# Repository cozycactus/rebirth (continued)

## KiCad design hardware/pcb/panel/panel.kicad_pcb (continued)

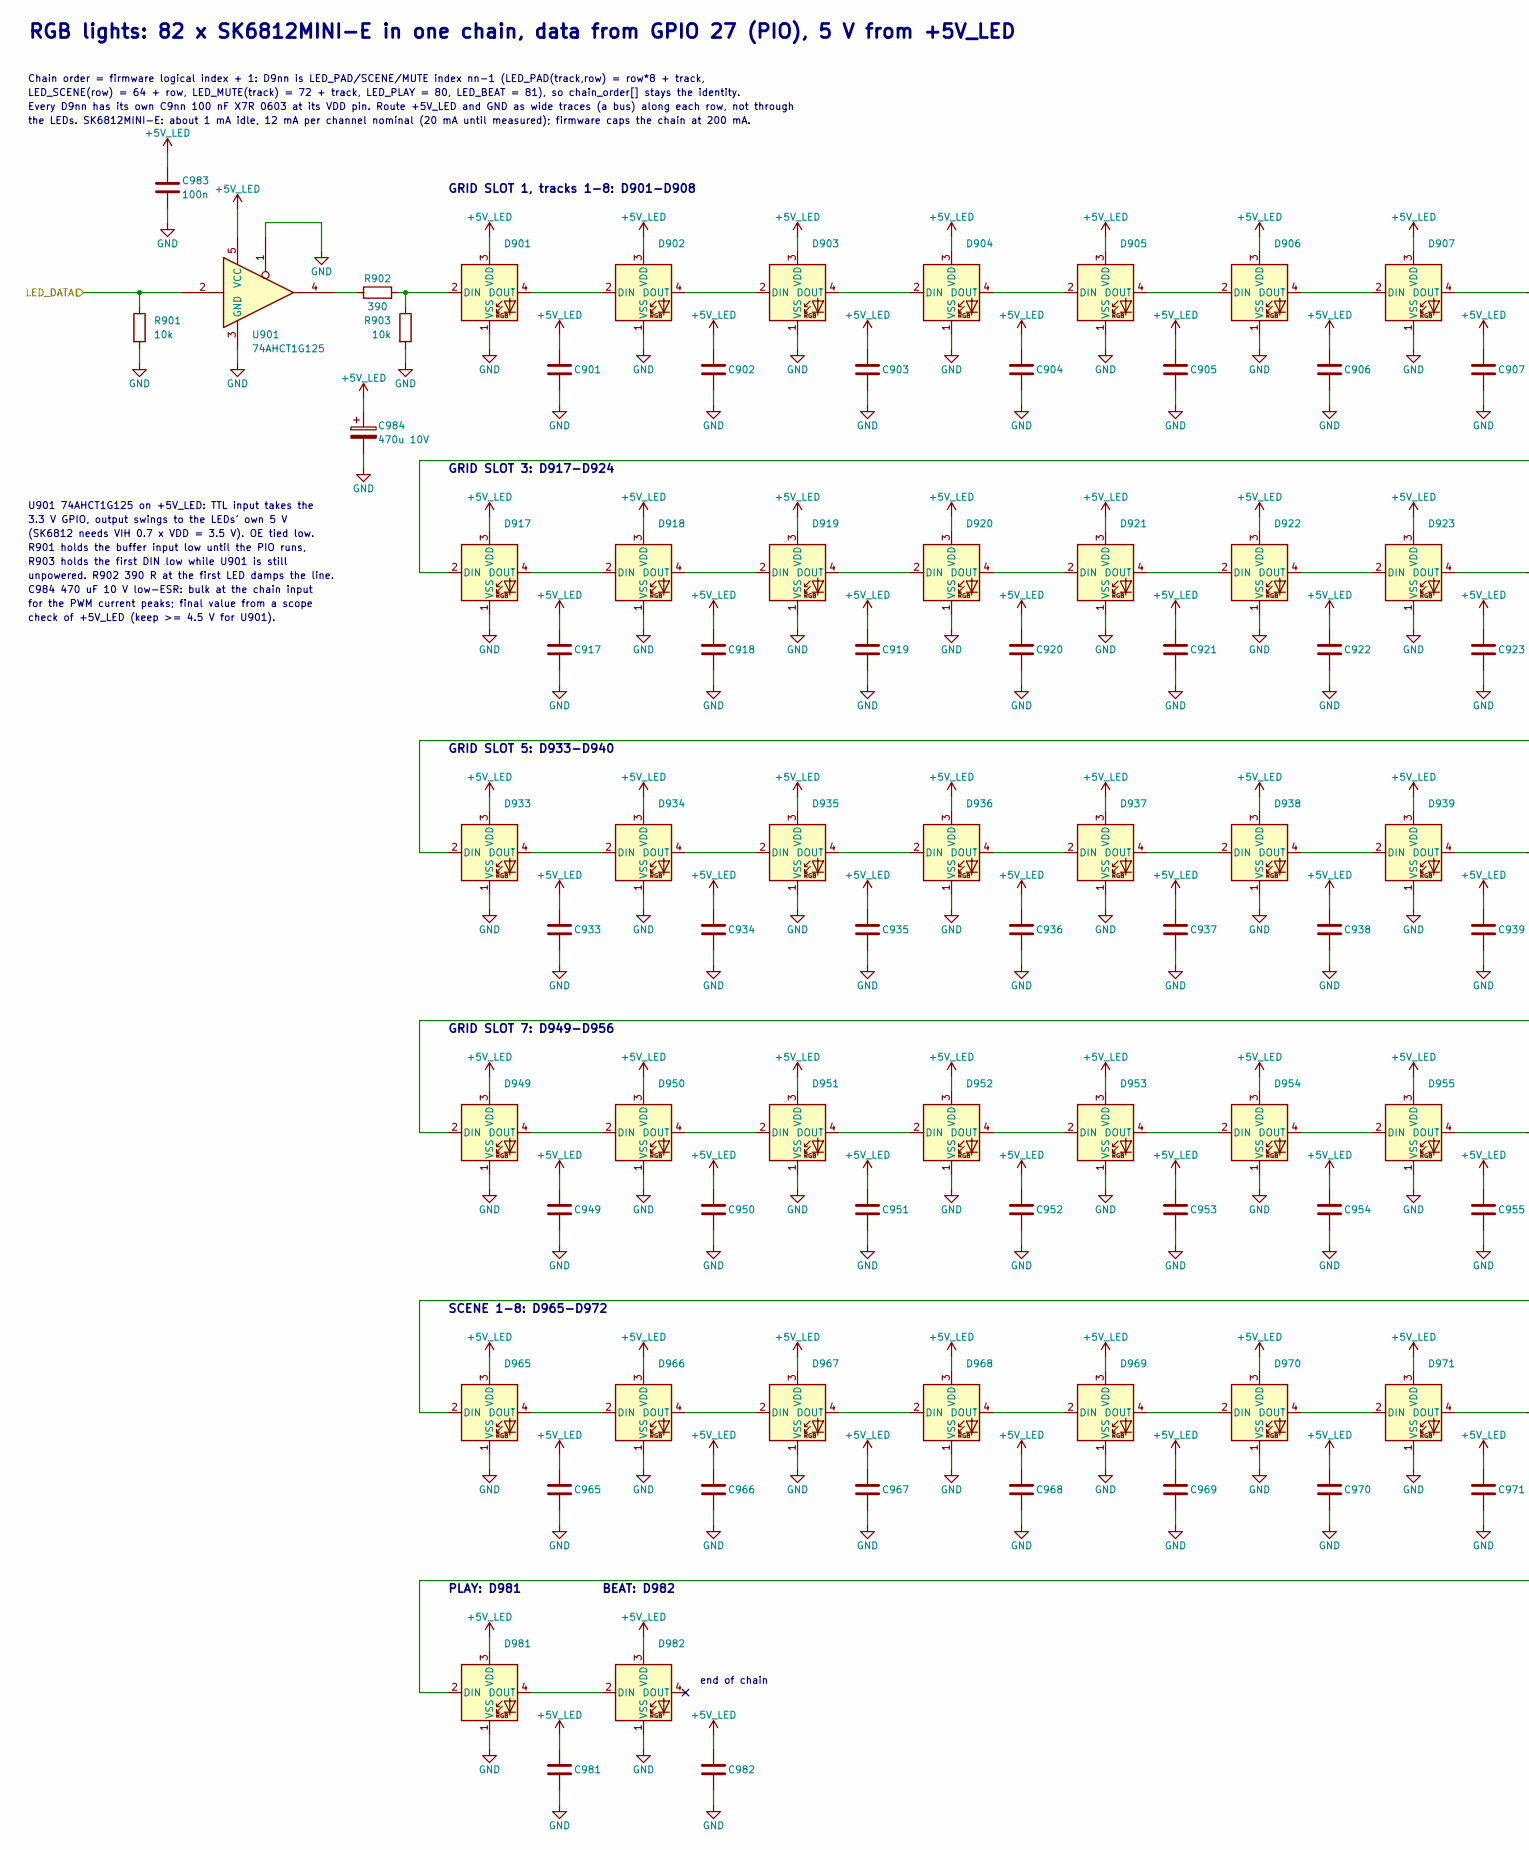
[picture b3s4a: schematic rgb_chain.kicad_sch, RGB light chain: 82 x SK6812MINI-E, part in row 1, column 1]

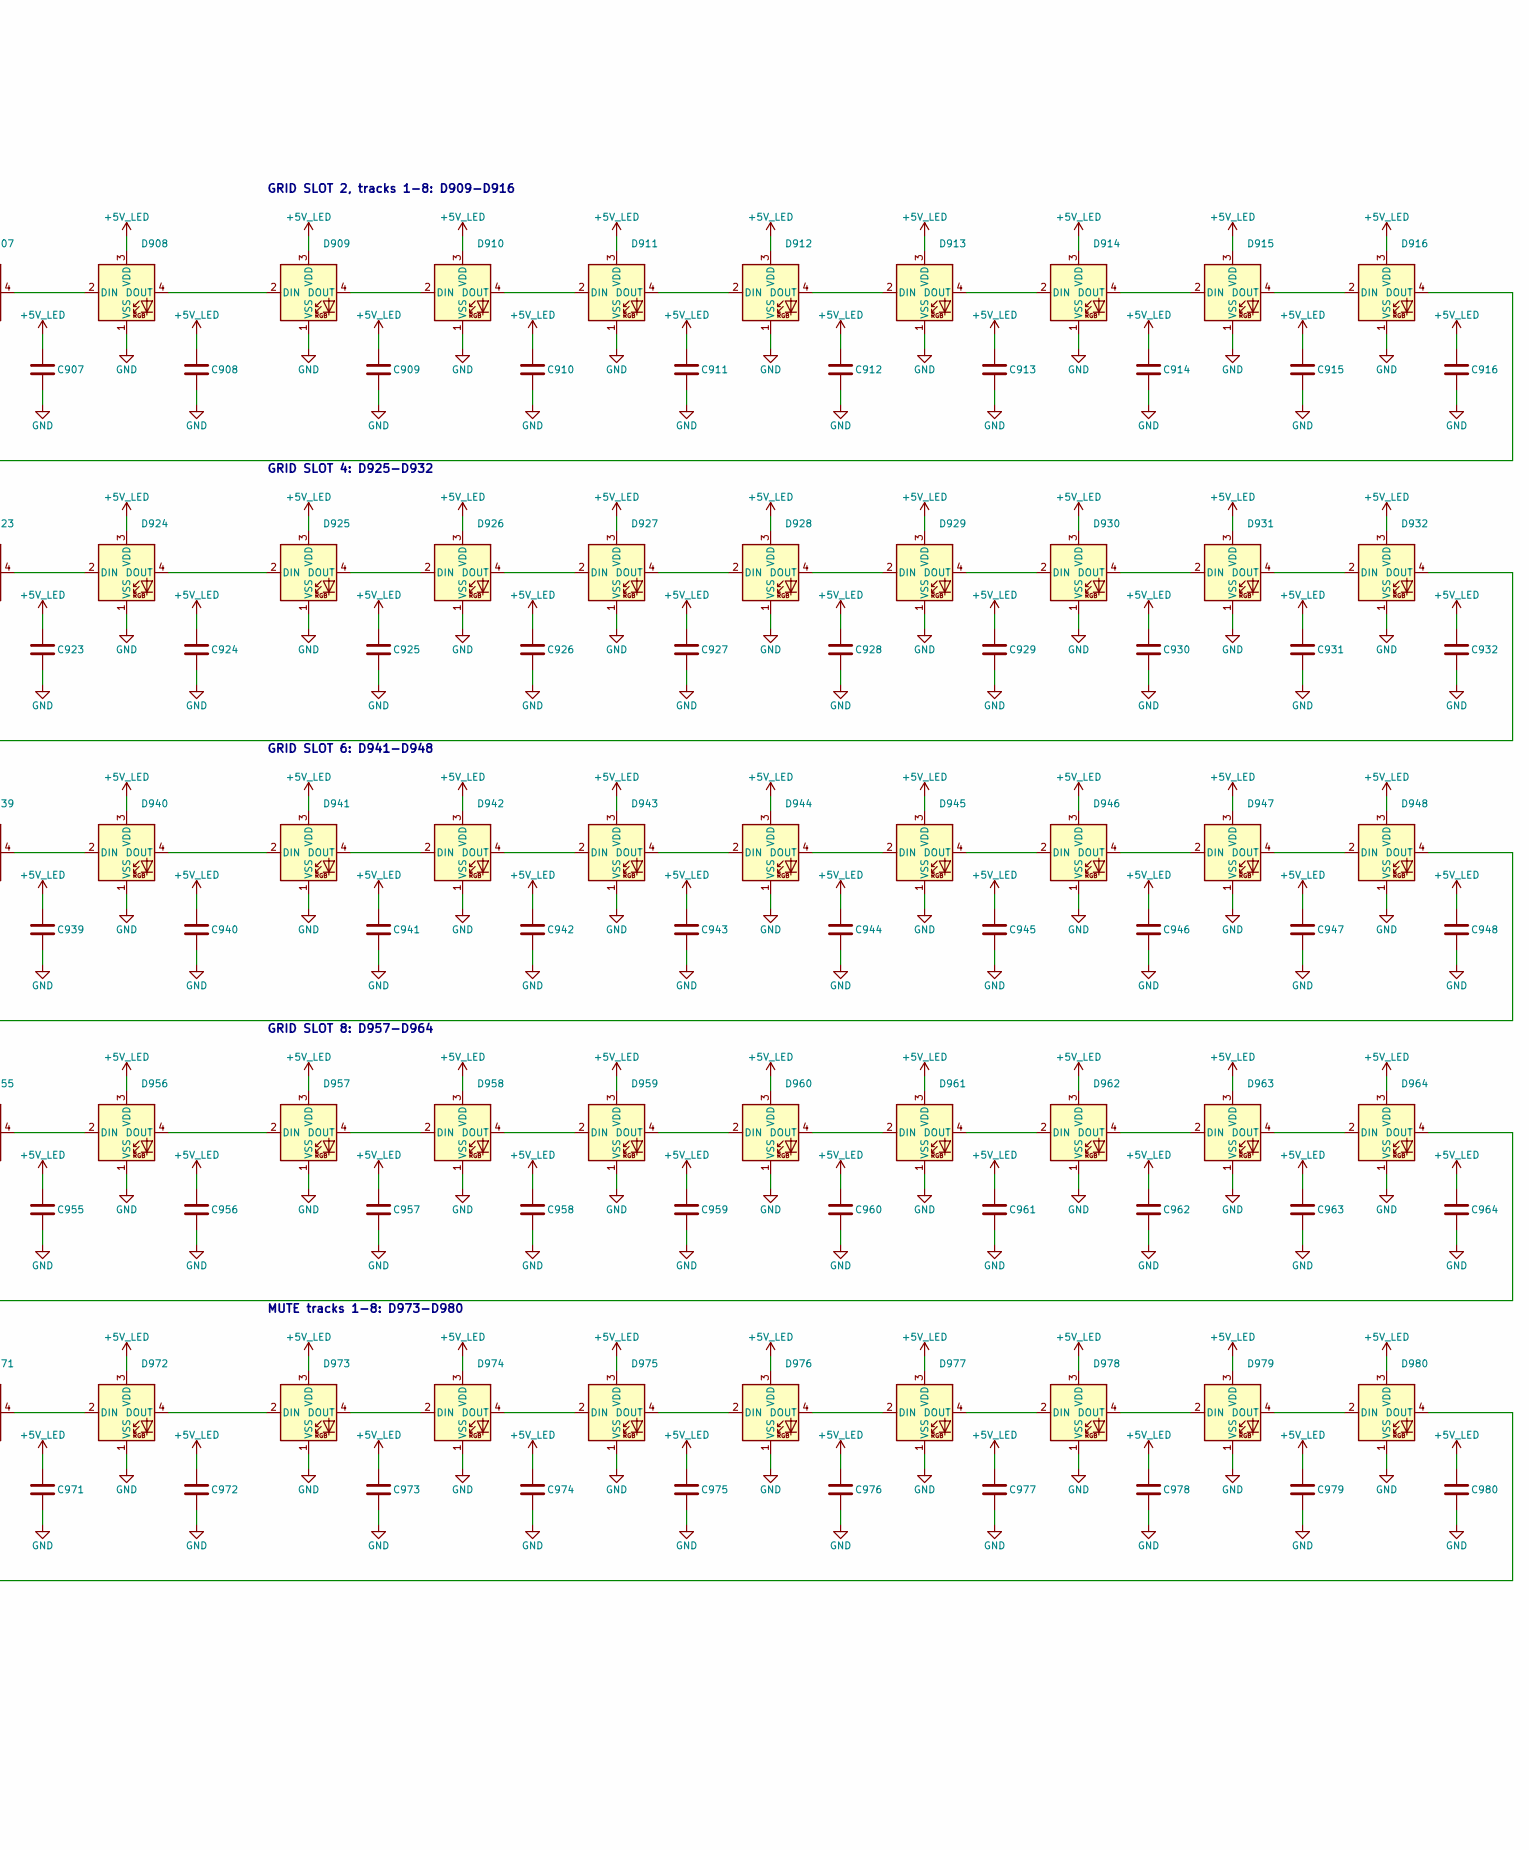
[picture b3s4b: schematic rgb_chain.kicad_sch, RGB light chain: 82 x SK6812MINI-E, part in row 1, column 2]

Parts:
C901, C902, C903, C904, C905, C906, C907, C908, C909, C910, C911, C912, C913, C914, C915, C916, C917, C918, C919, C920, C921, C922, C923, C924, C925, C926, C927, C928, C929, C930, C931, C932, C933, C934, C935, C936, C937, C938, C939, C940, C941, C942, C943, C944, C945, C946, C947, C948, C949, C950, C951, C952, C953, C954, C955, C956, C957, C958, C959, C960, C961, C962, C963, C964, C965, C966, C967, C968, C969, C970, C971, C972, C973, C974, C975, C976, C977, C978, C979, C980, C981, C982, C983: 100n; C_0603_1608Metric
C984: 470u 10V; CP_Elec_8x10
D901, D902, D903, D904, D905, D906, D907, D908, D909, D910, D911, D912, D913, D914, D915, D916, D917, D918, D919, D920, D921, D922, D923, D924, D925, D926, D927, D928, D929, D930, D931, D932, D933, D934, D935, D936, D937, D938, D939, D940, D941, D942, D943, D944, D945, D946, D947, D948, D949, D950, D951, D952, D953, D954, D955, D956, D957, D958, D959, D960, D961, D962, D963, D964, D965, D966, D967, D968, D969, D970, D971, D972, D973, D974, D975, D976, D977, D978, D979, D980, D981, D982: SK6812MINI-E; LED_SK6812MINI-E_3.2x2.8mm_P1.5mm_ReverseMount
R901, R903: 10k; R_0603_1608Metric
R902: 390; R_0603_1608Metric
U901: 74AHCT1G125; SOT-23-5

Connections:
+5V_LED: C901.1, C902.1, C903.1, C904.1, C905.1, C906.1, C907.1, C908.1, C909.1, C910.1, C911.1, C912.1, C913.1, C914.1, C915.1, C916.1, C917.1, C918.1, C919.1, C920.1, C921.1, C922.1, C923.1, C924.1, C925.1, C926.1, C927.1, C928.1, C929.1, C930.1, C931.1, C932.1, C933.1, C934.1, C935.1, C936.1, C937.1, C938.1, C939.1, C940.1, C941.1, C942.1, C943.1, C944.1, C945.1, C946.1, C947.1, C948.1, C949.1, C950.1, C951.1, C952.1, C953.1, C954.1, C955.1, C956.1, C957.1, C958.1, C959.1, C960.1, C961.1, C962.1, C963.1, C964.1, C965.1, C966.1, C967.1, C968.1, C969.1, C970.1, C971.1, C972.1, C973.1, C974.1, C975.1, C976.1, C977.1, C978.1, C979.1, C980.1, C981.1, C982.1, C983.1, C984.1, D901.3 (VDD), D902.3 (VDD), D903.3 (VDD), D904.3 (VDD), D905.3 (VDD), D906.3 (VDD), D907.3 (VDD), D908.3 (VDD), D909.3 (VDD), D910.3 (VDD), D911.3 (VDD), D912.3 (VDD), D913.3 (VDD), D914.3 (VDD), D915.3 (VDD), D916.3 (VDD), D917.3 (VDD), D918.3 (VDD), D919.3 (VDD), D920.3 (VDD), D921.3 (VDD), D922.3 (VDD), D923.3 (VDD), D924.3 (VDD), D925.3 (VDD), D926.3 (VDD), D927.3 (VDD), D928.3 (VDD), D929.3 (VDD), D930.3 (VDD), D931.3 (VDD), D932.3 (VDD), D933.3 (VDD), D934.3 (VDD), D935.3 (VDD), D936.3 (VDD), D937.3 (VDD), D938.3 (VDD), D939.3 (VDD), D940.3 (VDD), D941.3 (VDD), D942.3 (VDD), D943.3 (VDD), D944.3 (VDD), D945.3 (VDD), D946.3 (VDD), D947.3 (VDD), D948.3 (VDD), D949.3 (VDD), D950.3 (VDD), D951.3 (VDD), D952.3 (VDD), D953.3 (VDD), D954.3 (VDD), D955.3 (VDD), D956.3 (VDD), D957.3 (VDD), D958.3 (VDD), D959.3 (VDD), D960.3 (VDD), D961.3 (VDD), D962.3 (VDD), D963.3 (VDD), D964.3 (VDD), D965.3 (VDD), D966.3 (VDD), D967.3 (VDD), D968.3 (VDD), D969.3 (VDD), D970.3 (VDD), D971.3 (VDD), D972.3 (VDD), D973.3 (VDD), D974.3 (VDD), D975.3 (VDD), D976.3 (VDD), D977.3 (VDD), D978.3 (VDD), D979.3 (VDD), D980.3 (VDD), D981.3 (VDD), D982.3 (VDD), U901.5 (VCC); also elsewhere on the board
/LED_DATA: R901.1, U901.2; also elsewhere on the board
GND: C901.2, C902.2, C903.2, C904.2, C905.2, C906.2, C907.2, C908.2, C909.2, C910.2, C911.2, C912.2, C913.2, C914.2, C915.2, C916.2, C917.2, C918.2, C919.2, C920.2, C921.2, C922.2, C923.2, C924.2, C925.2, C926.2, C927.2, C928.2, C929.2, C930.2, C931.2, C932.2, C933.2, C934.2, C935.2, C936.2, C937.2, C938.2, C939.2, C940.2, C941.2, C942.2, C943.2, C944.2, C945.2, C946.2, C947.2, C948.2, C949.2, C950.2, C951.2, C952.2, C953.2, C954.2, C955.2, C956.2, C957.2, C958.2, C959.2, C960.2, C961.2, C962.2, C963.2, C964.2, C965.2, C966.2, C967.2, C968.2, C969.2, C970.2, C971.2, C972.2, C973.2, C974.2, C975.2, C976.2, C977.2, C978.2, C979.2, C980.2, C981.2, C982.2, C983.2, C984.2, D901.1 (VSS), D902.1 (VSS), D903.1 (VSS), D904.1 (VSS), D905.1 (VSS), D906.1 (VSS), D907.1 (VSS), D908.1 (VSS), D909.1 (VSS), D910.1 (VSS), D911.1 (VSS), D912.1 (VSS), D913.1 (VSS), D914.1 (VSS), D915.1 (VSS), D916.1 (VSS), D917.1 (VSS), D918.1 (VSS), D919.1 (VSS), D920.1 (VSS), D921.1 (VSS), D922.1 (VSS), D923.1 (VSS), D924.1 (VSS), D925.1 (VSS), D926.1 (VSS), D927.1 (VSS), D928.1 (VSS), D929.1 (VSS), D930.1 (VSS), D931.1 (VSS), D932.1 (VSS), D933.1 (VSS), D934.1 (VSS), D935.1 (VSS), D936.1 (VSS), D937.1 (VSS), D938.1 (VSS), D939.1 (VSS), D940.1 (VSS), D941.1 (VSS), D942.1 (VSS), D943.1 (VSS), D944.1 (VSS), D945.1 (VSS), D946.1 (VSS), D947.1 (VSS), D948.1 (VSS), D949.1 (VSS), D950.1 (VSS), D951.1 (VSS), D952.1 (VSS), D953.1 (VSS), D954.1 (VSS), D955.1 (VSS), D956.1 (VSS), D957.1 (VSS), D958.1 (VSS), D959.1 (VSS), D960.1 (VSS), D961.1 (VSS), D962.1 (VSS), D963.1 (VSS), D964.1 (VSS), D965.1 (VSS), D966.1 (VSS), D967.1 (VSS), D968.1 (VSS), D969.1 (VSS), D970.1 (VSS), D971.1 (VSS), D972.1 (VSS), D973.1 (VSS), D974.1 (VSS), D975.1 (VSS), D976.1 (VSS), D977.1 (VSS), D978.1 (VSS), D979.1 (VSS), D980.1 (VSS), D981.1 (VSS), D982.1 (VSS), R901.2, R903.2, U901.1, U901.3 (GND); also elsewhere on the board
unnamed: D901.2 (DIN), R902.2, R903.1
unnamed: D901.4 (DOUT), D902.2 (DIN)
unnamed: D902.4 (DOUT), D903.2 (DIN)
unnamed: D903.4 (DOUT), D904.2 (DIN)
unnamed: D904.4 (DOUT), D905.2 (DIN)
unnamed: D905.4 (DOUT), D906.2 (DIN)
unnamed: D906.4 (DOUT), D907.2 (DIN)
unnamed: D907.4 (DOUT), D908.2 (DIN)
unnamed: D908.4 (DOUT), D909.2 (DIN)
unnamed: D909.4 (DOUT), D910.2 (DIN)
unnamed: D910.4 (DOUT), D911.2 (DIN)
unnamed: D911.4 (DOUT), D912.2 (DIN)
unnamed: D912.4 (DOUT), D913.2 (DIN)
unnamed: D913.4 (DOUT), D914.2 (DIN)
unnamed: D914.4 (DOUT), D915.2 (DIN)
unnamed: D915.4 (DOUT), D916.2 (DIN)
unnamed: D916.4 (DOUT), D917.2 (DIN)
unnamed: D917.4 (DOUT), D918.2 (DIN)
unnamed: D918.4 (DOUT), D919.2 (DIN)
unnamed: D919.4 (DOUT), D920.2 (DIN)
unnamed: D920.4 (DOUT), D921.2 (DIN)
unnamed: D921.4 (DOUT), D922.2 (DIN)
unnamed: D922.4 (DOUT), D923.2 (DIN)
unnamed: D923.4 (DOUT), D924.2 (DIN)
unnamed: D924.4 (DOUT), D925.2 (DIN)
unnamed: D925.4 (DOUT), D926.2 (DIN)
unnamed: D926.4 (DOUT), D927.2 (DIN)
unnamed: D927.4 (DOUT), D928.2 (DIN)
unnamed: D928.4 (DOUT), D929.2 (DIN)
unnamed: D929.4 (DOUT), D930.2 (DIN)
unnamed: D930.4 (DOUT), D931.2 (DIN)
unnamed: D931.4 (DOUT), D932.2 (DIN)
unnamed: D932.4 (DOUT), D933.2 (DIN)
unnamed: D933.4 (DOUT), D934.2 (DIN)
unnamed: D934.4 (DOUT), D935.2 (DIN)
unnamed: D935.4 (DOUT), D936.2 (DIN)
unnamed: D936.4 (DOUT), D937.2 (DIN)
unnamed: D937.4 (DOUT), D938.2 (DIN)
unnamed: D938.4 (DOUT), D939.2 (DIN)
unnamed: D939.4 (DOUT), D940.2 (DIN)
unnamed: D940.4 (DOUT), D941.2 (DIN)
unnamed: D941.4 (DOUT), D942.2 (DIN)
unnamed: D942.4 (DOUT), D943.2 (DIN)
unnamed: D943.4 (DOUT), D944.2 (DIN)
unnamed: D944.4 (DOUT), D945.2 (DIN)
unnamed: D945.4 (DOUT), D946.2 (DIN)
unnamed: D946.4 (DOUT), D947.2 (DIN)
unnamed: D947.4 (DOUT), D948.2 (DIN)
unnamed: D948.4 (DOUT), D949.2 (DIN)
unnamed: D949.4 (DOUT), D950.2 (DIN)
unnamed: D950.4 (DOUT), D951.2 (DIN)
unnamed: D951.4 (DOUT), D952.2 (DIN)
unnamed: D952.4 (DOUT), D953.2 (DIN)
unnamed: D953.4 (DOUT), D954.2 (DIN)
unnamed: D954.4 (DOUT), D955.2 (DIN)
unnamed: D955.4 (DOUT), D956.2 (DIN)
unnamed: D956.4 (DOUT), D957.2 (DIN)
unnamed: D957.4 (DOUT), D958.2 (DIN)
unnamed: D958.4 (DOUT), D959.2 (DIN)
unnamed: D959.4 (DOUT), D960.2 (DIN)
unnamed: D960.4 (DOUT), D961.2 (DIN)
unnamed: D961.4 (DOUT), D962.2 (DIN)
unnamed: D962.4 (DOUT), D963.2 (DIN)
unnamed: D963.4 (DOUT), D964.2 (DIN)
unnamed: D964.4 (DOUT), D965.2 (DIN)
unnamed: D965.4 (DOUT), D966.2 (DIN)
unnamed: D966.4 (DOUT), D967.2 (DIN)
unnamed: D967.4 (DOUT), D968.2 (DIN)
unnamed: D968.4 (DOUT), D969.2 (DIN)
unnamed: D969.4 (DOUT), D970.2 (DIN)
unnamed: D970.4 (DOUT), D971.2 (DIN)
unnamed: D971.4 (DOUT), D972.2 (DIN)
unnamed: D972.4 (DOUT), D973.2 (DIN)
unnamed: D973.4 (DOUT), D974.2 (DIN)
unnamed: D974.4 (DOUT), D975.2 (DIN)
unnamed: D975.4 (DOUT), D976.2 (DIN)
unnamed: D976.4 (DOUT), D977.2 (DIN)
unnamed: D977.4 (DOUT), D978.2 (DIN)
unnamed: D978.4 (DOUT), D979.2 (DIN)
unnamed: D979.4 (DOUT), D980.2 (DIN)
unnamed: D980.4 (DOUT), D981.2 (DIN)
unnamed: D981.4 (DOUT), D982.2 (DIN)
unnamed: R902.1, U901.4

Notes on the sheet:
RGB lights: 82 x SK6812MINI-E in one chain, data from GPIO 27 (PIO), 5 V from +5V_LED
Chain order = firmware logical index + 1: D9nn is LED_PAD/SCENE/MUTE index nn-1 (LED_PAD(track,row) = row*8 + track,
LED_SCENE(row) = 64 + row, LED_MUTE(track) = 72 + track, LED_PLAY = 80, LED_BEAT = 81), so chain_order[] stays the identity.
Every D9nn has its own C9nn 100 nF X7R 0603 at its VDD pin. Route +5V_LED and GND as wide traces (a bus) along each row, not through
the LEDs. SK6812MINI-E: about 1 mA idle, 12 mA per channel nominal (20 mA until measured); firmware caps the chain at 200 mA.
U901 74AHCT1G125 on +5V_LED: TTL input takes the
3.3 V GPIO, output swings to the LEDs' own 5 V
(SK6812 needs VIH 0.7 x VDD = 3.5 V). OE tied low.
R901 holds the buffer input low until the PIO runs,
R903 holds the first DIN low while U901 is still
unpowered. R902 390 R at the first LED damps the line.
C984 470 uF 10 V low-ESR: bulk at the chain input
for the PWM current peaks; final value from a scope
check of +5V_LED (keep >= 4.5 V for U901).
end of chain
GRID SLOT 1, tracks 1-8: D901-D908
GRID SLOT 2, tracks 1-8: D909-D916
GRID SLOT 3: D917-D924
GRID SLOT 4: D925-D932
GRID SLOT 5: D933-D940
GRID SLOT 6: D941-D948
GRID SLOT 7: D949-D956
GRID SLOT 8: D957-D964
SCENE 1-8: D965-D972
MUTE tracks 1-8: D973-D980
PLAY: D981
BEAT: D982

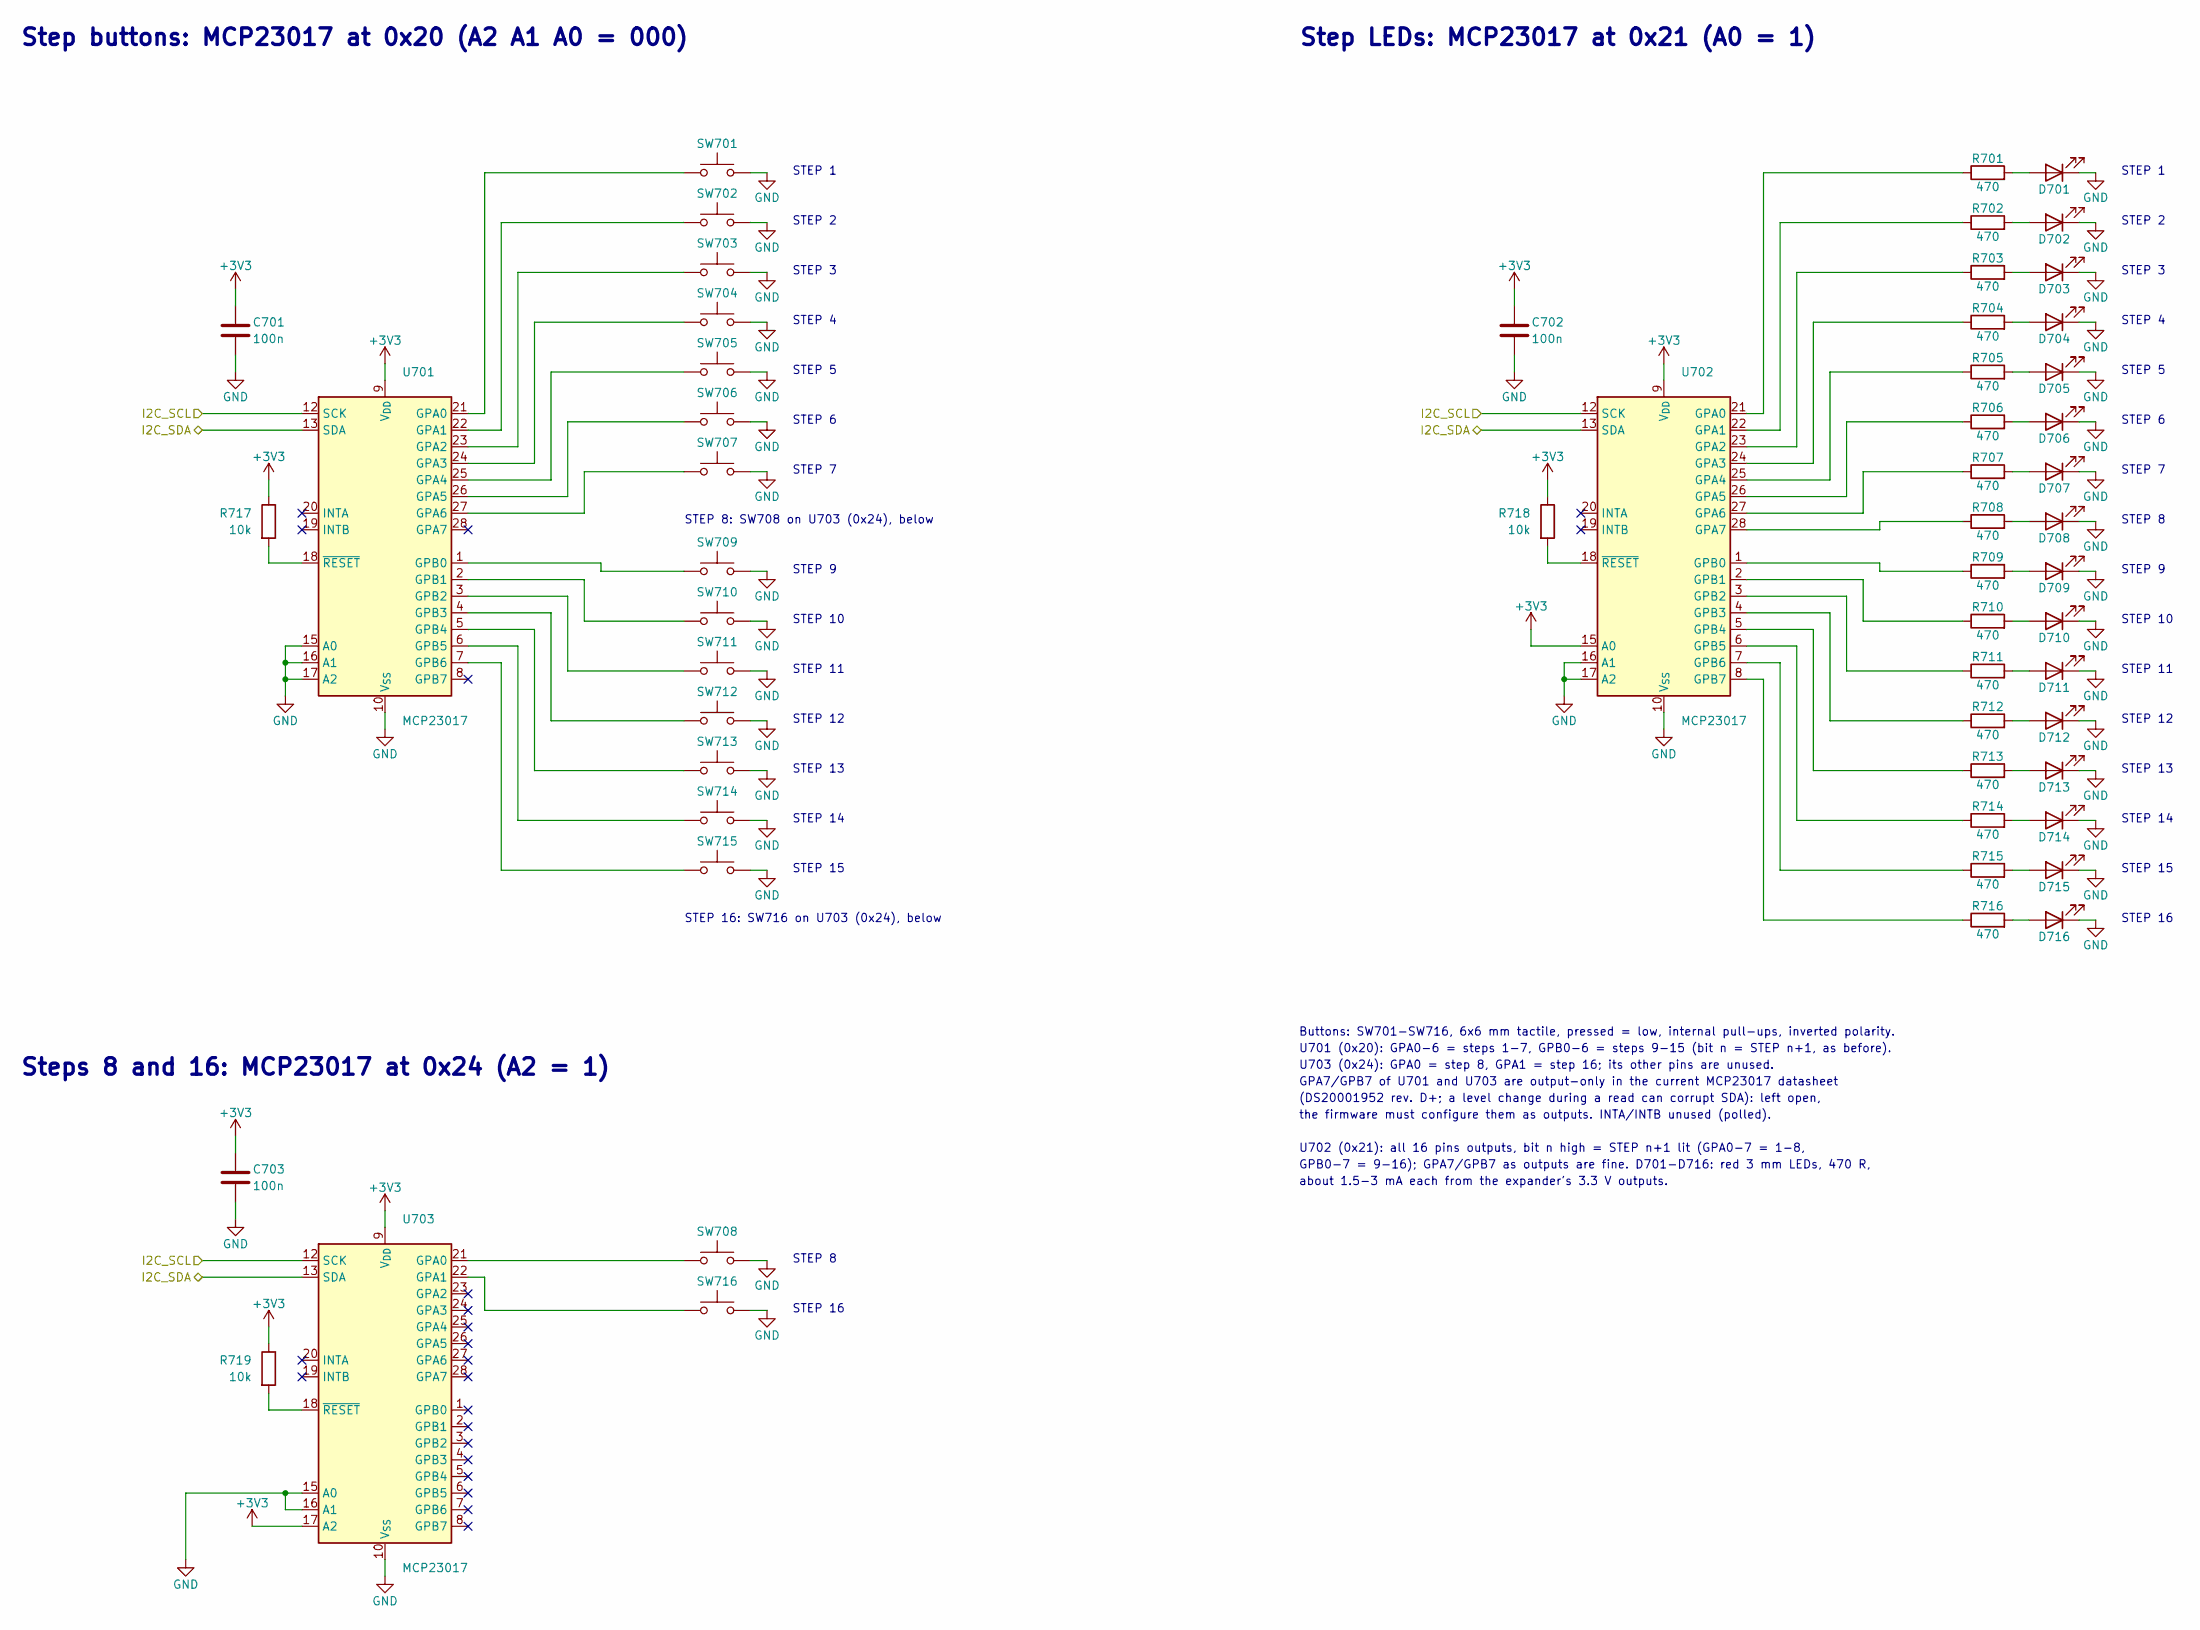
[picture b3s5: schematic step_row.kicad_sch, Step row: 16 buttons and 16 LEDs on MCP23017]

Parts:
C701, C702, C703: 100n; C_0603_1608Metric
D701, D702, D703, D704, D705, D706, D707, D708, D709, D710, D711, D712, D713, D714, D715, D716: RED; LED_D3.0mm
R701, R702, R703, R704, R705, R706, R707, R708, R709, R710, R711, R712, R713, R714, R715, R716: 470; R_0603_1608Metric
R717, R718, R719: 10k; R_0603_1608Metric
SW701: STEP 1; SW_PUSH_6mm
SW702: STEP 2; SW_PUSH_6mm
SW703: STEP 3; SW_PUSH_6mm
SW704: STEP 4; SW_PUSH_6mm
SW705: STEP 5; SW_PUSH_6mm
SW706: STEP 6; SW_PUSH_6mm
SW707: STEP 7; SW_PUSH_6mm
SW708: STEP 8; SW_PUSH_6mm
SW709: STEP 9; SW_PUSH_6mm
SW710: STEP 10; SW_PUSH_6mm
SW711: STEP 11; SW_PUSH_6mm
SW712: STEP 12; SW_PUSH_6mm
SW713: STEP 13; SW_PUSH_6mm
SW714: STEP 14; SW_PUSH_6mm
SW715: STEP 15; SW_PUSH_6mm
SW716: STEP 16; SW_PUSH_6mm
U701, U702, U703: MCP23017; SOIC-28W_7.5x17.9mm_P1.27mm

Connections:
+3V3: C701.1, C702.1, C703.1, R717.1, R718.1, R719.1, U701.9 (V_{DD}), U702.9 (V_{DD}), U702.15 (A0), U703.9 (V_{DD}), U703.17 (A2); also elsewhere on the board
/I2C_SCL: U701.12 (SCK), U702.12 (SCK), U703.12 (SCK); also elsewhere on the board
/I2C_SDA: U701.13 (SDA), U702.13 (SDA), U703.13 (SDA); also elsewhere on the board
GND: C701.2, C702.2, C703.2, D701.1 (K), D702.1 (K), D703.1 (K), D704.1 (K), D705.1 (K), D706.1 (K), D707.1 (K), D708.1 (K), D709.1 (K), D710.1 (K), D711.1 (K), D712.1 (K), D713.1 (K), D714.1 (K), D715.1 (K), D716.1 (K), SW701.2, SW702.2, SW703.2, SW704.2, SW705.2, SW706.2, SW707.2, SW708.2, SW709.2, SW710.2, SW711.2, SW712.2, SW713.2, SW714.2, SW715.2, SW716.2, U701.10 (V_{SS}), U701.15 (A0), U701.16 (A1), U701.17 (A2), U702.10 (V_{SS}), U702.16 (A1), U702.17 (A2), U703.10 (V_{SS}), U703.15 (A0), U703.16 (A1); also elsewhere on the board
unnamed: D701.2 (A), R701.2
unnamed: D702.2 (A), R702.2
unnamed: D703.2 (A), R703.2
unnamed: D704.2 (A), R704.2
unnamed: D705.2 (A), R705.2
unnamed: D706.2 (A), R706.2
unnamed: D707.2 (A), R707.2
unnamed: D708.2 (A), R708.2
unnamed: D709.2 (A), R709.2
unnamed: D710.2 (A), R710.2
unnamed: D711.2 (A), R711.2
unnamed: D712.2 (A), R712.2
unnamed: D713.2 (A), R713.2
unnamed: D714.2 (A), R714.2
unnamed: D715.2 (A), R715.2
unnamed: D716.2 (A), R716.2
unnamed: SW701.1, U701.21 (GPA0)
unnamed: SW702.1, U701.22 (GPA1)
unnamed: SW703.1, U701.23 (GPA2)
unnamed: SW704.1, U701.24 (GPA3)
unnamed: SW705.1, U701.25 (GPA4)
unnamed: SW706.1, U701.26 (GPA5)
unnamed: SW707.1, U701.27 (GPA6)
unnamed: SW709.1, U701.1 (GPB0)
unnamed: SW710.1, U701.2 (GPB1)
unnamed: SW711.1, U701.3 (GPB2)
unnamed: SW712.1, U701.4 (GPB3)
unnamed: SW713.1, U701.5 (GPB4)
unnamed: SW714.1, U701.6 (GPB5)
unnamed: SW715.1, U701.7 (GPB6)
unnamed: R717.2, U701.18 (~RESET)
unnamed: R701.1, U702.21 (GPA0)
unnamed: R702.1, U702.22 (GPA1)
unnamed: R703.1, U702.23 (GPA2)
unnamed: R704.1, U702.24 (GPA3)
unnamed: R705.1, U702.25 (GPA4)
unnamed: R706.1, U702.26 (GPA5)
unnamed: R707.1, U702.27 (GPA6)
unnamed: R708.1, U702.28 (GPA7)
unnamed: R709.1, U702.1 (GPB0)
unnamed: R710.1, U702.2 (GPB1)
unnamed: R711.1, U702.3 (GPB2)
unnamed: R712.1, U702.4 (GPB3)
unnamed: R713.1, U702.5 (GPB4)
unnamed: R714.1, U702.6 (GPB5)
unnamed: R715.1, U702.7 (GPB6)
unnamed: R716.1, U702.8 (GPB7)
unnamed: R718.2, U702.18 (~RESET)
unnamed: SW708.1, U703.21 (GPA0)
unnamed: SW716.1, U703.22 (GPA1)
unnamed: R719.2, U703.18 (~RESET)

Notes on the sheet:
Step buttons: MCP23017 at 0x20 (A2 A1 A0 = 000)
Step LEDs: MCP23017 at 0x21 (A0 = 1)
STEP 1
STEP 2
STEP 3
STEP 4
STEP 5
STEP 6
STEP 7
STEP 8: SW708 on U703 (0x24), below
STEP 9
STEP 10
STEP 11
STEP 12
STEP 13
STEP 14
STEP 15
STEP 16: SW716 on U703 (0x24), below
STEP 8
STEP 16
Steps 8 and 16: MCP23017 at 0x24 (A2 = 1)
Buttons: SW701-SW716, 6x6 mm tactile, pressed = low, internal pull-ups, inverted polarity.
U701 (0x20): GPA0-6 = steps 1-7, GPB0-6 = steps 9-15 (bit n = STEP n+1, as before).
U703 (0x24): GPA0 = step 8, GPA1 = step 16; its other pins are unused.
GPA7/GPB7 of U701 and U703 are output-only in the current MCP23017 datasheet
(DS20001952 rev. D+; a level change during a read can corrupt SDA): left open,
the firmware must configure them as outputs. INTA/INTB unused (polled).
U702 (0x21): all 16 pins outputs, bit n high = STEP n+1 lit (GPA0-7 = 1-8,
GPB0-7 = 9-16); GPA7/GPB7 as outputs are fine. D701-D716: red 3 mm LEDs, 470 R,
about 1.5-3 mA each from the expander's 3.3 V outputs.

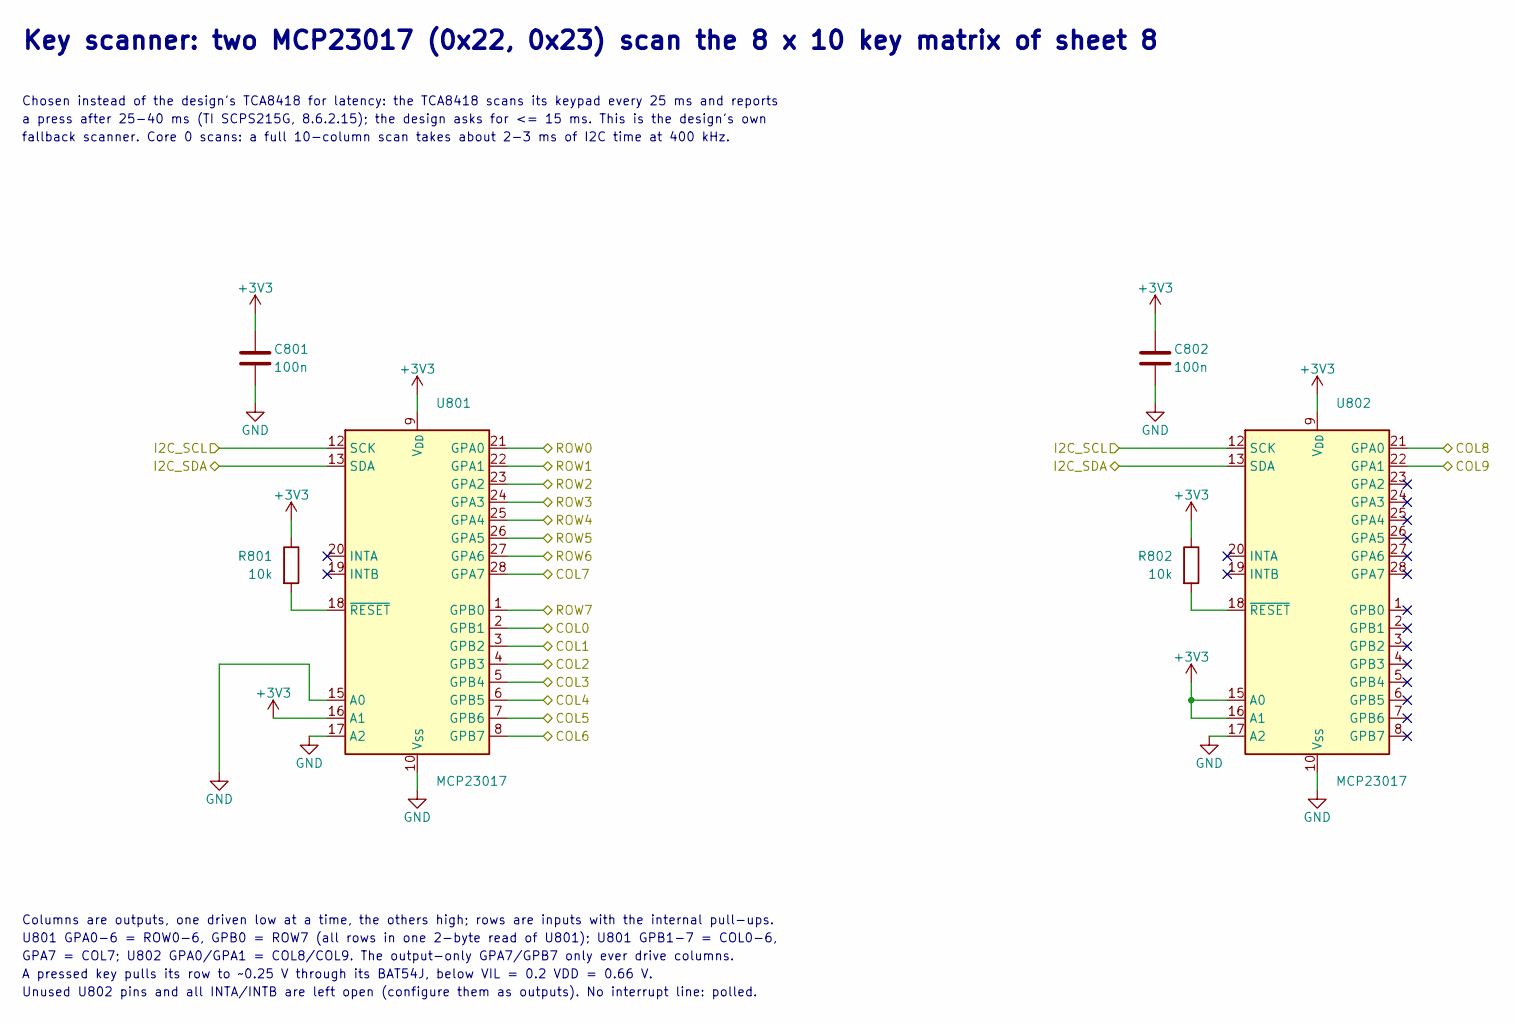
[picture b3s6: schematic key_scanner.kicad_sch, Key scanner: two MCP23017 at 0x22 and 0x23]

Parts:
C801, C802: 100n; C_0603_1608Metric
R801, R802: 10k; R_0603_1608Metric
U801, U802: MCP23017; SOIC-28W_7.5x17.9mm_P1.27mm

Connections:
+3V3: C801.1, C802.1, R801.1, R802.1, U801.9 (V_{DD}), U801.16 (A1), U802.9 (V_{DD}), U802.15 (A0), U802.16 (A1); also elsewhere on the board
/COL0: U801.2 (GPB1); also elsewhere on the board
/COL1: U801.3 (GPB2); also elsewhere on the board
/COL2: U801.4 (GPB3); also elsewhere on the board
/COL3: U801.5 (GPB4); also elsewhere on the board
/COL4: U801.6 (GPB5); also elsewhere on the board
/COL5: U801.7 (GPB6); also elsewhere on the board
/COL6: U801.8 (GPB7); also elsewhere on the board
/COL7: U801.28 (GPA7); also elsewhere on the board
/COL8: U802.21 (GPA0); also elsewhere on the board
/COL9: U802.22 (GPA1); also elsewhere on the board
/I2C_SCL: U801.12 (SCK), U802.12 (SCK); also elsewhere on the board
/I2C_SDA: U801.13 (SDA), U802.13 (SDA); also elsewhere on the board
/ROW0: U801.21 (GPA0); also elsewhere on the board
/ROW1: U801.22 (GPA1); also elsewhere on the board
/ROW2: U801.23 (GPA2); also elsewhere on the board
/ROW3: U801.24 (GPA3); also elsewhere on the board
/ROW4: U801.25 (GPA4); also elsewhere on the board
/ROW5: U801.26 (GPA5); also elsewhere on the board
/ROW6: U801.27 (GPA6); also elsewhere on the board
/ROW7: U801.1 (GPB0); also elsewhere on the board
GND: C801.2, C802.2, U801.10 (V_{SS}), U801.15 (A0), U801.17 (A2), U802.10 (V_{SS}), U802.17 (A2); also elsewhere on the board
unnamed: R801.2, U801.18 (~RESET)
unnamed: R802.2, U802.18 (~RESET)

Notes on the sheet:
Key scanner: two MCP23017 (0x22, 0x23) scan the 8 x 10 key matrix of sheet 8
Chosen instead of the design's TCA8418 for latency: the TCA8418 scans its keypad every 25 ms and reports
a press after 25-40 ms (TI SCPS215G, 8.6.2.15); the design asks for <= 15 ms. This is the design's own
fallback scanner. Core 0 scans: a full 10-column scan takes about 2-3 ms of I2C time at 400 kHz.
Columns are outputs, one driven low at a time, the others high; rows are inputs with the internal pull-ups.
U801 GPA0-6 = ROW0-6, GPB0 = ROW7 (all rows in one 2-byte read of U801); U801 GPB1-7 = COL0-6,
GPA7 = COL7; U802 GPA0/GPA1 = COL8/COL9. The output-only GPA7/GPB7 only ever drive columns.
A pressed key pulls its row to ~0.25 V through its BAT54J, below VIL = 0.2 VDD = 0.66 V.
Unused U802 pins and all INTA/INTB are left open (configure them as outputs). No interrupt line: polled.
